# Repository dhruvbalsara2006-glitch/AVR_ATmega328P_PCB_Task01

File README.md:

# AVR ATmega328P PCB Design using KiCad

A custom PCB design for the **ATmega328P microcontroller** created using **KiCad** as part of a PCB Design assignment. This project demonstrates schematic capture, PCB layout, component placement, and routing while following basic PCB design principles.

---

## 📖 Project Overview

This project focuses on designing a PCB for the **ATmega328P**, one of the most widely used AVR microcontrollers. The design includes the essential circuitry required to interface with the microcontroller and serves as a foundation for embedded system development.

---

## ✨ Features

- PCB designed using **KiCad**
- ATmega328P-based circuit
- Schematic capture
- PCB layout and routing
- Organized project files
- ATmega328P datasheet included

---

## 🛠️ Tools Used

- **KiCad**
- **ATmega328P Microcontroller**

---

## 📂 Repository Contents

```
AVR_ATmega328P_Board.kicad_pro      → KiCad project file
AVR_ATmega328P_Board.kicad_sch      → Schematic
AVR_ATmega328P_Board.kicad_pcb      → PCB layout
AVR_ATmega328P_Board.kicad_prl      → Project settings
ATMEGA48P.PDF                       → ATmega328P Datasheet
```

---

## 📷 Project Preview

> Screenshots of the schematic and PCB layout will be added soon.

---

## 🎯 Learning Outcomes

Through this project, I learned:

- PCB design workflow using KiCad
- Electronic schematic design
- PCB routing techniques
- Component placement considerations
- PCB project organization

---

## 🚀 Future Improvements

- Add 3D PCB renders
- Improve PCB routing
- Perform Design Rule Check (DRC)
- Add Gerber files
- Build and test the physical PCB

---

## 👨‍💻 Author

**Dhruv Balsara**

Electronics & Telecommunication Engineering Student

Dwarkadas J. Sanghvi College of Engineering (DJSCE)

🔗 LinkedIn: https://www.linkedin.com/in/dhruvbalsara-djsce

📧 Email: dhruvbalsara2006@gmail.com

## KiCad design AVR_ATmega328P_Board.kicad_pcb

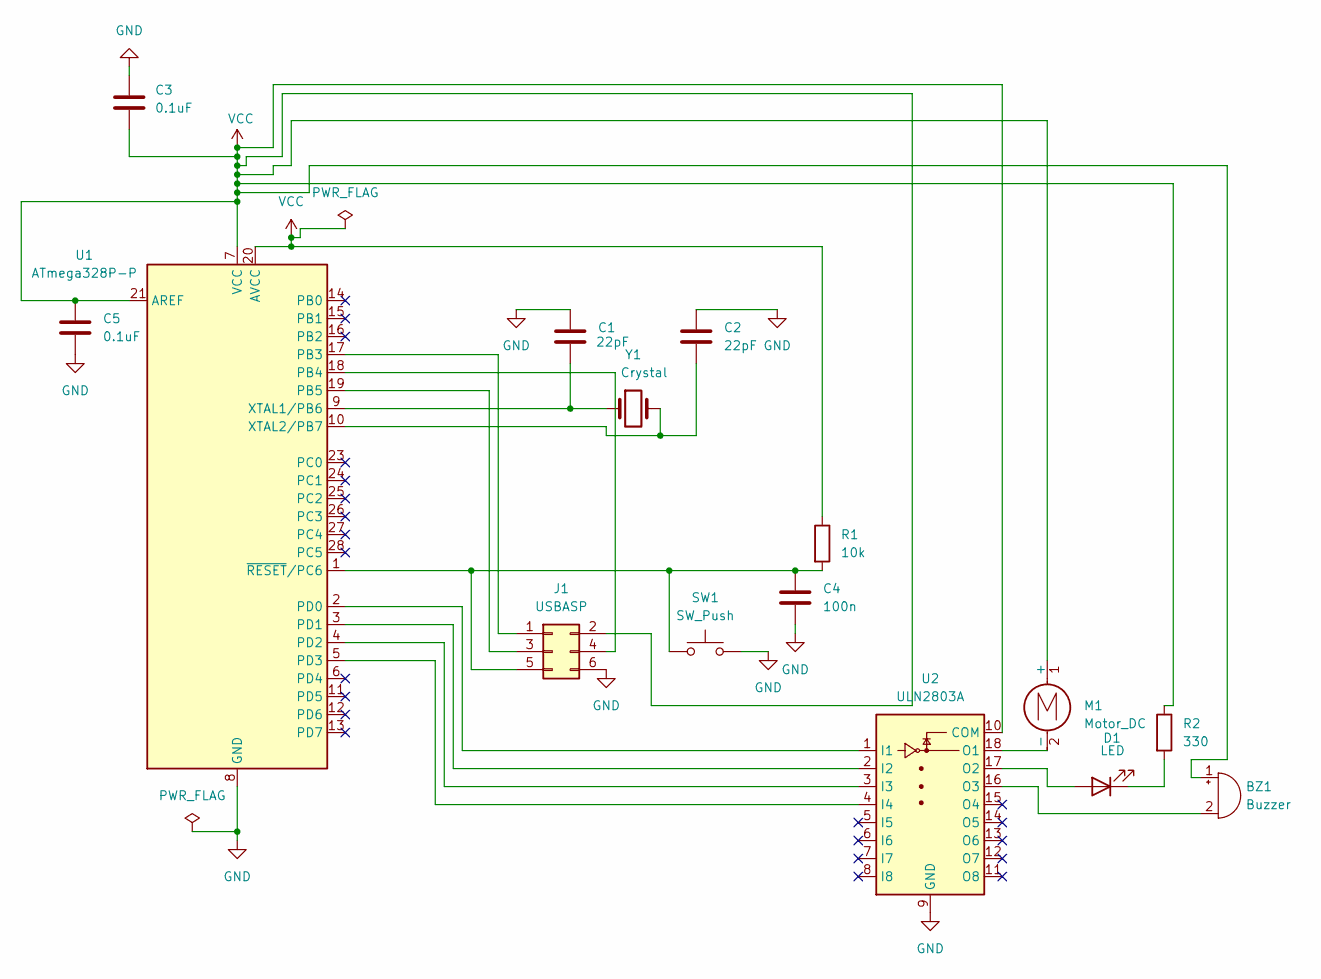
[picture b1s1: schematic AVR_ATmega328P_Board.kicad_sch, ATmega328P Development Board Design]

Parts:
BZ1: Buzzer; Buzzer_12x9.5RM7.6
C1, C2: 22pF; C_Disc_D5.0mm_W2.5mm_P2.50mm
C3, C5: 0.1uF; C_Disc_D5.0mm_W2.5mm_P2.50mm
C4: 100n; C_Disc_D5.0mm_W2.5mm_P2.50mm
D1: LED; LED_D5.0mm
J1: USBASP; PinHeader_2x03_P2.54mm_Horizontal
M1: Motor_DC; PinHeader_1x02_P2.54mm_Vertical
R1: 10k; R_Axial_DIN0207_L6.3mm_D2.5mm_P7.62mm_Horizontal
R2: 330; R_Axial_DIN0207_L6.3mm_D2.5mm_P7.62mm_Horizontal
SW1: SW_Push; SW_PUSH_6mm
U1: ATmega328P-P; DIP-28_W7.62mm
U2: ULN2803A; DIP-18_W7.62mm
Y1: Crystal; Crystal_HC49-U_Vertical

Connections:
GND: C1.1, C2.1, C3.1, C4.2, C5.2, J1.6, SW1.2, U1.8 (GND), U1.22 (GND), U2.9 (GND)
unnamed: BZ1.2 (-), U2.16 (O3)
unnamed: D1.2 (A), U2.17 (O2)
unnamed: D1.1 (K), R2.2
unnamed: J1.1, U1.17 (PB3)
unnamed: J1.3, U1.19 (PB5)
unnamed: J1.4, U1.18 (PB4)
unnamed: C4.1, J1.5, R1.2, SW1.1, U1.1 (~RESET/PC6)
unnamed: M1.2 (-), U2.18 (O1)
unnamed: U1.2 (PD0), U2.1 (I1)
unnamed: U1.3 (PD1), U2.2 (I2)
unnamed: U1.4 (PD2), U2.3 (I3)
unnamed: U1.5 (PD3), U2.4 (I4)
unnamed: C1.2, U1.9 (XTAL1/PB6), Y1.1
unnamed: C2.2, U1.10 (XTAL2/PB7), Y1.2
VCC: BZ1.1 (+), C3.2, C5.1, J1.2, M1.1 (+), R1.1, R2.1, U1.7 (VCC), U1.20 (AVCC), U1.21 (AREF), U2.10 (COM)

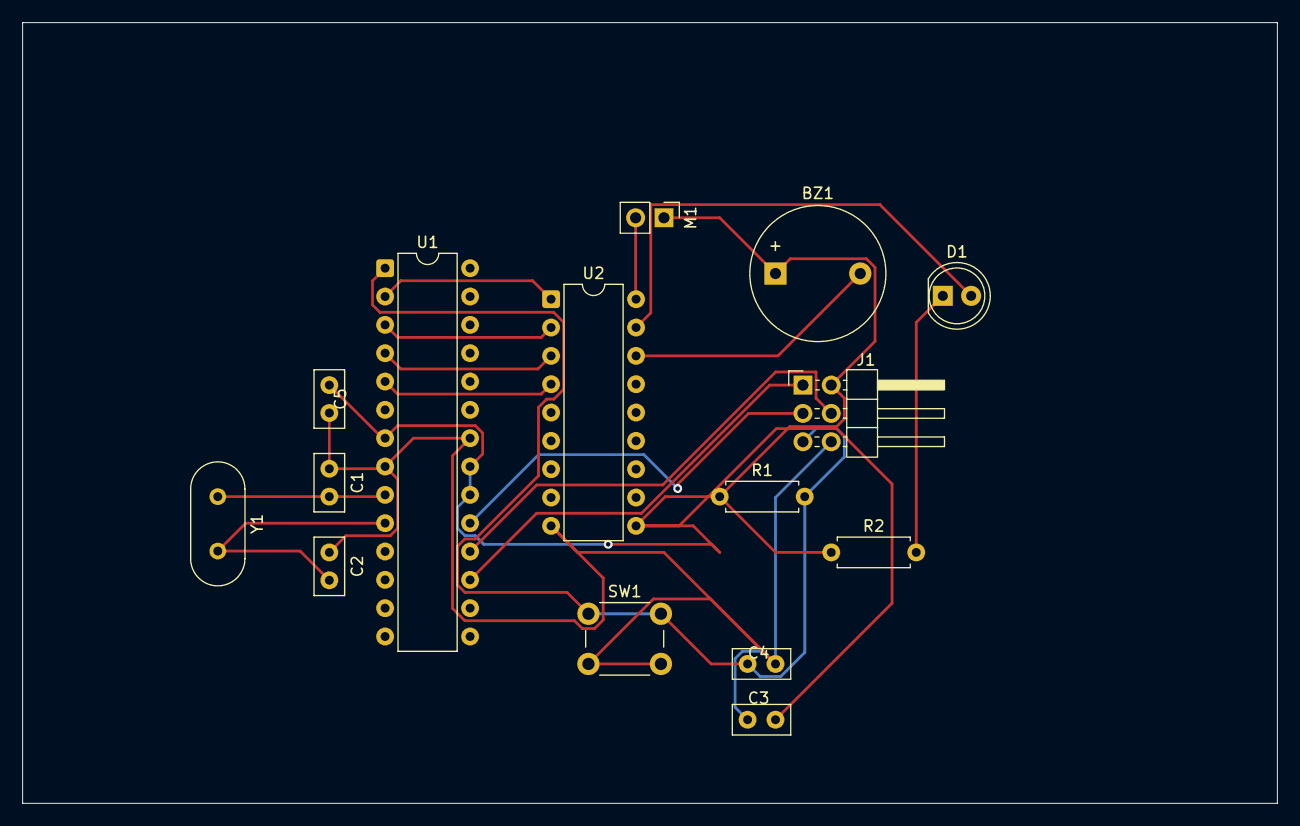
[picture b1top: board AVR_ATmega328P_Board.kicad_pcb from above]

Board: 2 copper layers, 112.5 x 70.0 mm, 15 parts (0 on the bottom side), 16 nets.

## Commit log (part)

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2026-02-24 Initial upload – ATmega328P PCB design (Task 01)
2026-02-24 Added ATmega328P datasheet
2026-02-24 Dhruv_ATmega328P_Design.pdf
